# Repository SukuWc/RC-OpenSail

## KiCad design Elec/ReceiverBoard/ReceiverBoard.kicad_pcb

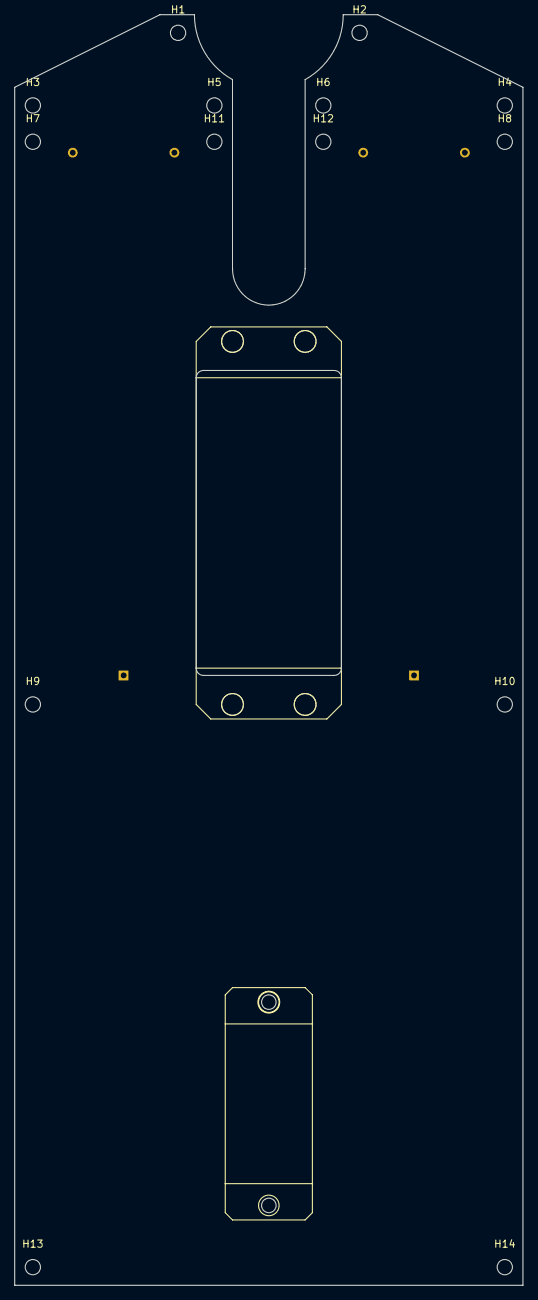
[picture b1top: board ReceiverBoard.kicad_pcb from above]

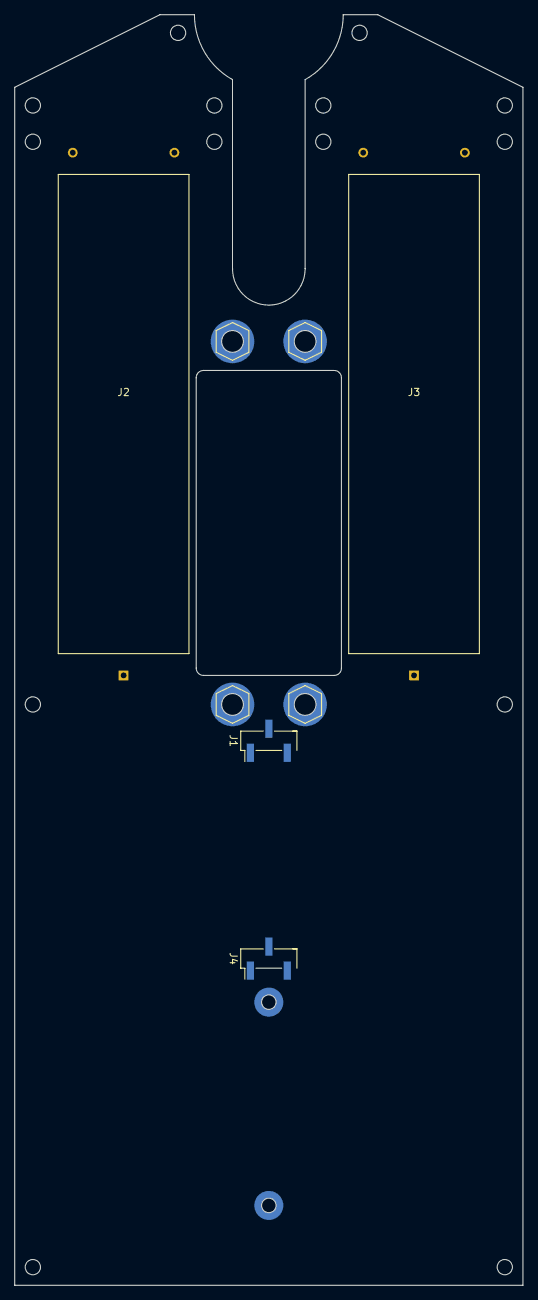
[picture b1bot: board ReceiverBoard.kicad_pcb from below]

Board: 2 copper layers, 70.0 x 175.0 mm, 18 parts (2 on the bottom side), 3 nets, no tracks yet.

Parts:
H1, H2, H3, H4, H5, H6, H7, H8, H9, H10, H11, H12, H13, H14: MountingHole; MountingHole_2.1mm
J1: Conn_01x03; SERVO_STANDARD
J2, J3: Conn_01x03; BATTERY_2X_18650
J4: Conn_01x03; SERVO_MICRO

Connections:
/BLACK: J1.3, J4.3
/ORANGE: J1.1, J4.1
/RED: J1.2, J4.2

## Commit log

2019-09-07 SUKU Repo init w/ Mono360
2019-09-07 SUKU rudder mock up added
2019-09-09 SUKU nose print
2020-01-26 SUKU Mono360 sync
2020-02-21 SUKU receiver board init
2020-02-26 SUKU sync
2020-03-16 SUKU ReceiverBoard created
2020-05-05 SUKU ocat init
2020-05-06 SUKU o-cat loft update
2020-05-07 SUKU ocat sync
2020-05-11 SUKU o-cat asm
